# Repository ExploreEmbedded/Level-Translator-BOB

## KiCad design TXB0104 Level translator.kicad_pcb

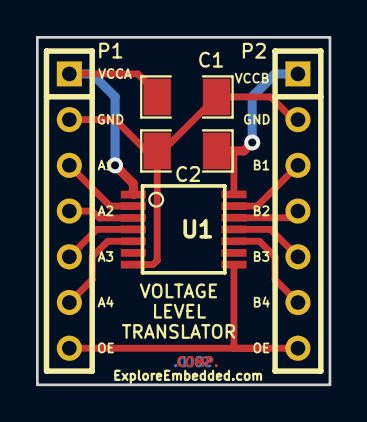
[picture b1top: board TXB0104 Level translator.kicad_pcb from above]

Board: 2 copper layers, 16.3 x 19.3 mm, 5 parts (0 on the bottom side), 12 nets.

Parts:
C1, C2: 0.1uF; SM1206
P1, P2: CONN_7; SIL-7
U1: TXB0104; SSOP14

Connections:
+3.3VP: C1.2, P1.1, U1.1
+5V: C2.1, P2.1, U1.14
/OE: P1.7, P2.7, U1.8
GND: C1.1, C2.2, P1.2, P2.2, U1.7
unnamed: P1.3, U1.2
unnamed: P1.4, U1.3
unnamed: P1.5, U1.4
unnamed: P1.6, U1.5
unnamed: P2.3, U1.13
unnamed: P2.4, U1.12
unnamed: P2.5, U1.11
unnamed: P2.6, U1.10

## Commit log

2015-06-17 test
2015-06-18 Ready for manufacturing
